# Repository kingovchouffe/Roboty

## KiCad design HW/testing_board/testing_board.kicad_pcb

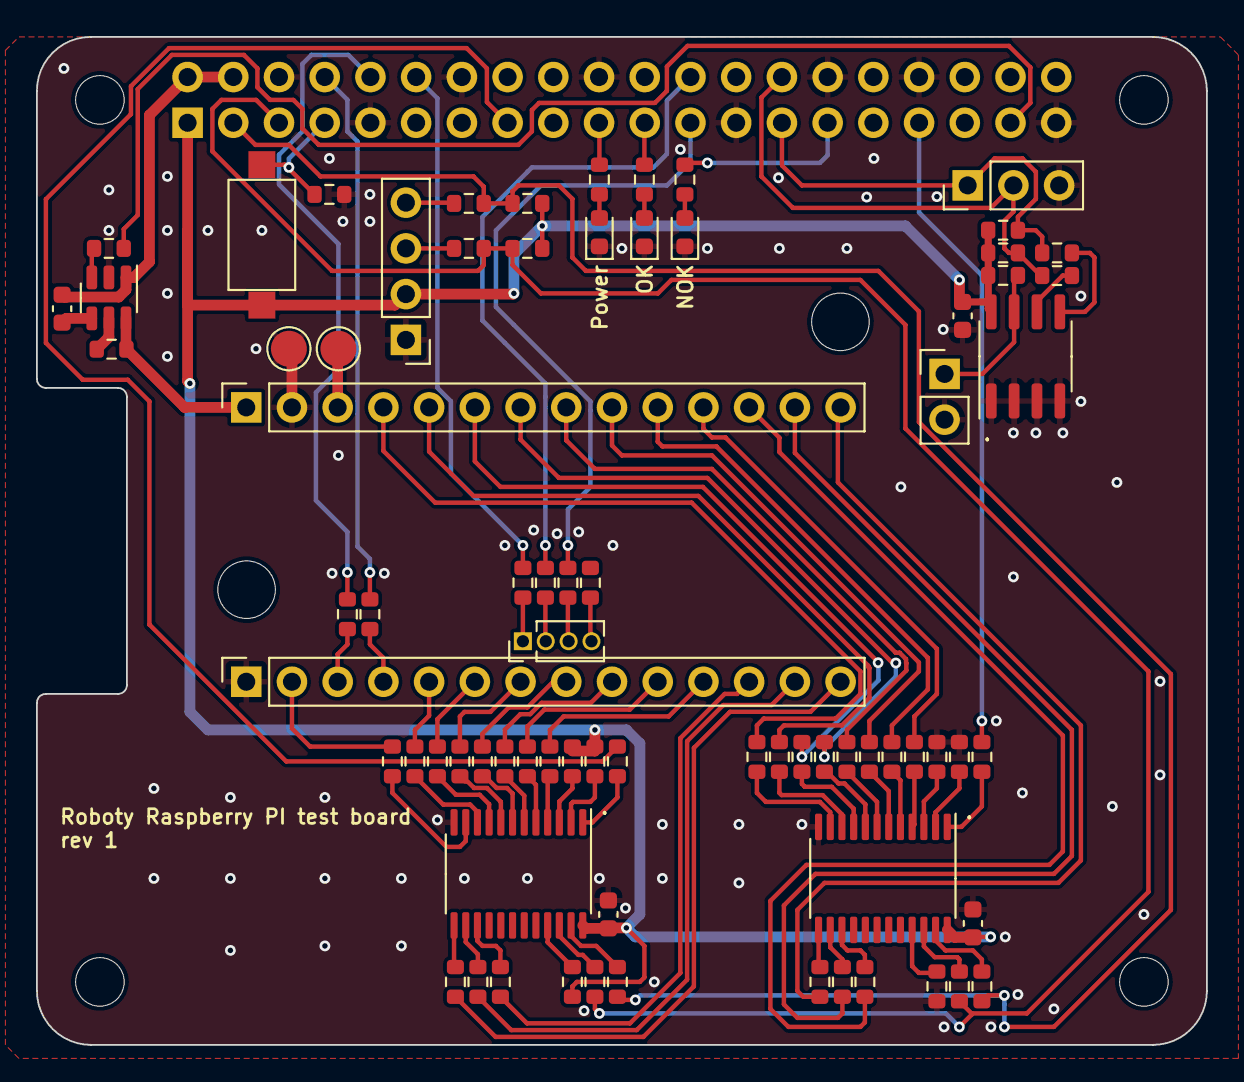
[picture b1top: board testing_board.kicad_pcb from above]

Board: 2 copper layers, 65.0 x 56.0 mm, 82 parts (1 on the bottom side), 94 nets.

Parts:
C1: C_0603_1608Metric
C2, C3, C4: 100n; C_0603_1608Metric
D1: LED_Power; LED_0603_1608Metric
D2: LED_testOK; LED_0603_1608Metric
D3: LED_testNOK; LED_0603_1608Metric
H1, H2: MountingHole; MountingHole_3.2mm_M3_ISO14580
J1: GPIO; PinSocket_2x20_P2.54mm_Vertical
J2: Left_; PinSocket_1x14_P2.54mm_Vertical
J3: Right_; PinSocket_1x14_P2.54mm_Vertical
J4: SWD; PinHeader_1x04_P1.27mm_Vertical
J5: OLED; PinHeader_1x04_P2.54mm_Vertical
J6: WP_jumper; PinHeader_1x02_P2.54mm_Vertical
J7: I2C_prob; PinHeader_1x03_P2.54mm_Vertical
MH1, MH2, MH3, MH4: MountingHole_2.7mm_M2.5
R1, R4, R5, R13, R14, R15, R16, R17, R18, R19, R20, R21, R22, R23, R24, R25, R26, R27, R28, R29, R30, R31, R32, R33, R34, R35, R42, R43, R44, R45, R46, R48: 1k; R_0603_1608Metric
R2, R3, R6, R7, R8, R9, R10, R11, R12, R36, R37, R38, R39, R40, R41, R54, R55: 0; R_0603_1608Metric
R47, R49, R50, R51, R52, R53: 10k; R_0603_1608Metric
SW1: Start; SW_SPST_CK_RS282G05A3
TP1: 3V3; TestPoint_Pad_D2.0mm
TP2: GND; TestPoint_Pad_D2.0mm
U1: TPS22917DBV; SOT-23-6
U2, U5: TCA9555PWR; TSSOP-24_4.4x7.8mm_P0.65mm
U3: CAT24C32; SOIC-8_3.9x4.9mm_P1.27mm

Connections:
+3V3: C2.1, C3.1, C4.1, J1.1, J5.2, R4.1, R5.2, R42.1, R49.2, R50.1, R51.1, R52.1, R53.1, SW1.1, U2.24 (VCC), U3.8 (VCC), U5.24 (VCC)
+5V: C1.1, J1.2, J1.4, U1.1 (VIN)
/A2: R39.1, U2.23 (SDA)
/B2: R40.2, U2.22 (SCL)
/C2: R41.1, U2.1 (~INT)
/GPIO2/SDA1: J1.3, R3.1, R36.2, R39.2, R49.1
/GPIO3/SCL1: J1.5, R2.2, R37.1, R40.1, R50.2
/GPIO4/GPCLK0: J1.7, R47.2, SW1.2
/GPIO5: J1.29, R46.1
/GPIO8/SPI0.CE0: J1.24, R10.1
/GPIO9/SPI0.MISO: J1.21, R45.1
/GPIO10/SPI0.MOSI: J1.19, R13.1
/GPIO11/SPI0.SCLK: J1.23, R11.1
/GPIO13/PWM1: J1.33, R41.2
/GPIO14/TXD0: J1.8, R6.2
/GPIO15/RXD0: J1.10, R7.1
/GPIO18/PCM.CLK: J1.12, R9.1
/GPIO22: J1.15, R38.2
/GPIO26: J1.37, R8.1
/ID_SCL: J1.28, J7.2, R53.2, R55.1
/ID_SDA: J1.27, J7.1, R52.2, R54.2
/ON/OFF: R8.2, U1.3 (ON)
/RST: J4.1, R9.2
/SWCLK: J4.3, R11.2
/SWDIO: J4.2, R10.2
/SWO: J4.4, R12.2
/UART_RX: J2.4, R6.1
/UART_TX: J2.3, R7.2
GND: C2.2, C3.2, C4.2, D1.1 (K), D2.1 (K), D3.1 (K), J1.6, J1.9, J1.14, J1.20, J1.25, J1.30, J1.34, J1.39, J2.1, J3.2, J5.1, J6.2, J7.3, R43.1, R44.2, R47.1, R48.1, TP2.1, U1.2 (GND), U2.12 (GND), U3.1 (A0), U3.2 (A1), U3.3 (A2), U3.4 (GND), U5.12 (GND)
HDR_LFT_PA0: J2.8, R17.1
HDR_LFT_PA1: J2.7, R18.2
HDR_LFT_PA2: J2.6, R19.1
HDR_LFT_PA3: J2.5, R20.2
HDR_LFT_PA4: J3.11, R25.1
HDR_LFT_PA5: J3.10, R26.2
HDR_LFT_PA6: J3.9, R22.2
HDR_LFT_PA7: J3.8, R23.1
HDR_LFT_PA8: J2.2, R21.1
HDR_LFT_PA15: J2.9, R16.2
HDR_LFT_PB4: J2.10, R15.1
HDR_RGT_PB5: J2.11, R14.2
HDR_RGT_PB7: J2.12, R29.1
HDR_RGT_PB8: J2.13, R28.2
HDR_RGT_PB9: J2.14, R27.1
HDR_RGT_PB10: J3.7, R24.2
HDR_RGT_PB12: J3.6, R30.2
HDR_RGT_PB13: J3.5, R31.1
HDR_RGT_PB14: J3.4, R32.2
HDR_RGT_PB15: J3.12, R35.1
HDR_RGT_PC0: J3.14, R33.1
HDR_RGT_PC1: J3.13, R34.2
unnamed: D1.2 (A), R13.2
unnamed: D2.2 (A), R45.2
unnamed: D3.2 (A), R46.2
unnamed: J3.3, TP1.1
unnamed: J5.3, R2.1
unnamed: J5.4, R3.2
unnamed: J6.1, R51.2, U3.7 (WP)
unnamed: C1.2, U1.4 (CT)
unnamed: R1.2, U1.5 (QOD)
unnamed: R48.2, U2.21 (A0)
unnamed: R44.1, U2.2 (A1)
unnamed: R43.2, U2.3 (A2)
unnamed: R25.2, U2.4 (P00)
unnamed: R26.1, U2.5 (P01)
unnamed: R22.1, U2.6 (P02)
unnamed: R23.2, U2.7 (P03)
unnamed: R24.1, U2.8 (P04)
unnamed: R30.1, U2.9 (P05)
unnamed: R31.2, U2.10 (P06)
unnamed: R32.1, U2.11 (P07)
unnamed: R33.2, U2.13 (P10)
unnamed: R34.1, U2.14 (P11)
unnamed: R35.2, U2.15 (P12)
unnamed: R55.2, U3.6 (SCL)
unnamed: R54.1, U3.5 (SDA)
unnamed: R4.2, U5.21 (A0)
unnamed: R5.1, U5.2 (A1)
unnamed: R42.2, U5.3 (A2)
unnamed: R14.1, U5.4 (P00)
unnamed: R15.2, U5.5 (P01)
unnamed: R16.1, U5.6 (P02)
unnamed: R17.2, U5.7 (P03)
unnamed: R18.1, U5.8 (P04)
unnamed: R19.2, U5.9 (P05)
unnamed: R20.1, U5.10 (P06)
unnamed: R21.2, U5.11 (P07)
unnamed: R27.2, U5.13 (P10)
unnamed: R28.1, U5.14 (P11)
unnamed: R29.2, U5.15 (P12)
unnamed: R37.2, U5.22 (SCL)
unnamed: R36.1, U5.23 (SDA)
unnamed: R38.1, U5.1 (~INT)
VDC: J3.1, R1.1, U1.6 (VOUT)

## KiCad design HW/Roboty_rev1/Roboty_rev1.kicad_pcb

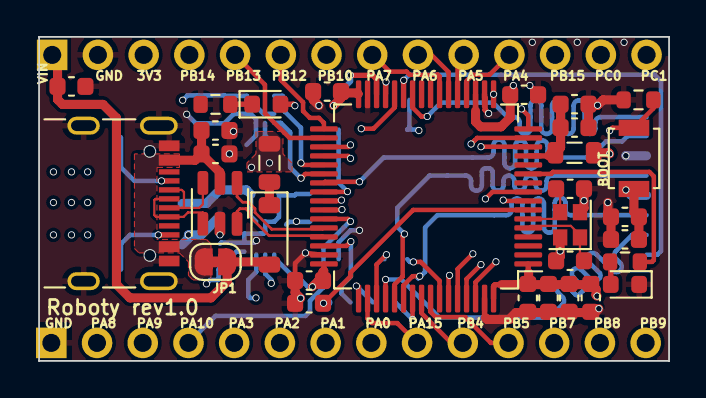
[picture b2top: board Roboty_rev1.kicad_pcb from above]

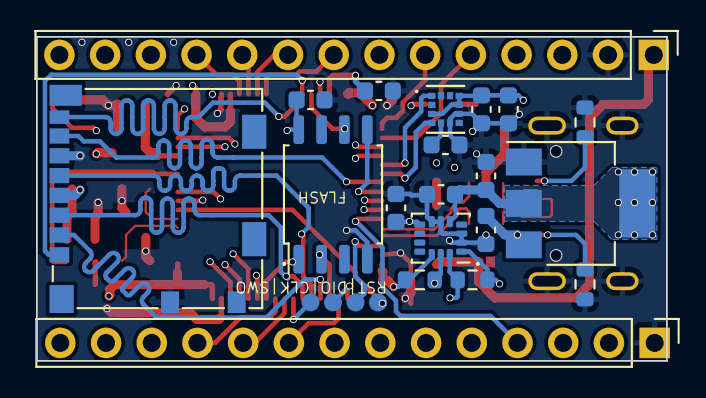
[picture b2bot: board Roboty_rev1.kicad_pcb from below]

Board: 6 copper layers, 35.0 x 18.0 mm, 55 parts (24 on the bottom side), 61 nets.

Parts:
C1, C4, C6, C11, C27: 10u; C_0603_1608Metric
C2, C3, C7, C8, C9, C10, C12, C13, C16, C19, C20, C21, C22, C23, C24, C25, C26: 100n; C_0603_1608Metric
C14: 1u; C_0603_1608Metric
C15: 4u7; C_0603_1608Metric
C17, C18: 6.8p; C_0603_1608Metric
D1: LED_33V; LED_0603_1608Metric
D2: SSS2040FL; D_SOD-123
D3: USER_LED; LED_0603_1608Metric
J1: Micro_SD_Card; microSD_HC_Molex_104031-0811
J3: USB_C_Receptacle_USB2.0; USB_C_Receptacle_GCT_USB4105-xx-A_16P_TopMnt_Horizontal
J4: Left_; PinHeader_1x14_P2.54mm_Vertical
J5: Right_; PinHeader_1x14_P2.54mm_Vertical
JP1: VUSB_VIN; SolderJumper-2_P1.3mm_Bridged_RoundedPad1.0x1.5mm
L1, L2: GZ2012D101TF; L_0805_2012Metric
R1, R2: 5.1k; R_0603_1608Metric
R3: 270; R_0603_1608Metric
R4, R6, R7: 10k; R_0603_1608Metric
R5: 1K; R_0603_1608Metric
SW2: BOOT; SW_SPST_B3U-1000P
TP1: SWO; TestPoint_Pad_D1.0mm
TP2: SWCLK; TestPoint_Pad_D1.0mm
TP3: SWDIO; TestPoint_Pad_D1.0mm
TP4: RST; TestPoint_Pad_D1.0mm
U1: STM32F446RETx; LQFP-64_10x10mm_P0.5mm
U2: NCP1117-3.3_SOT223; SOT-223-3_TabPin2
U3: USBLC6-2SC6; SOT-23-6
U4: W25Q32JVSS; SOIC-8_5.23x5.23mm_P1.27mm
U5: LSM6DS3; LGA-14_3x2.5mm_P0.5mm_LayoutBorder3x4y
U6: LIS2MDLTR; PQFN50P200X200X70-12N
Y1: 7D026000B01; Crystal_SMD_2016-4Pin_2.0x1.6mm

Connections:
+3V3: C3.1, C4.1, C7.1, C8.1, C9.1, C10.1, C11.1, C12.1, C19.1, C21.1, C22.1, C23.1, C24.1, C26.1, C27.1, D1.2 (A), J1.4 (VDD), J5.3, L2.2, R6.2, R7.1, SW2.1, U1.1 (VBAT), U1.19 (VDD), U1.32 (VDD), U1.48 (VDD), U1.64 (VDD), U2.2 (VO), U4.8 (VCC), U5.1 (SDO/SA0), U5.5 (VDDIO), U5.8 (VDD), U5.12 (CS), U6.3 (CS), U6.9 (VDD), U6.10 (VDD_IO)
+5V: C2.1, C6.1, J3.A4 (VBUS), J3.A9 (VBUS), J3.B4 (VBUS), J3.B9 (VBUS), JP1.1 (A), U3.5 (VBUS)
/I2C_SCL: R7.2, U1.37 (PC6), U5.13 (SCL), U6.1 (SCL/SPC)
/I2C_SDA: R6.1, U1.38 (PC7), U5.14 (SDA), U6.4 (SDA/SDI/SDO)
/Power&USB/USB+: U1.45 (PA12), U3.3 (I/O2)
/Power&USB/USB-: U1.44 (PA11), U3.4 (I/O2)
/mcu/BOOT0: R4.1, SW2.2, U1.60 (BOOT0)
/mcu/LED: R5.2, U1.11 (PC3)
/mcu/QSPI_BK1_CLK: U1.28 (PB2), U4.6 (CLK)
/mcu/QSPI_BK1_IO0: U1.40 (PC9), U4.5 (DI(IO0))
/mcu/QSPI_BK1_IO1: U1.51 (PC10), U4.2 (DO(IO1))
/mcu/QSPI_BK1_NCS: U1.58 (PB6), U4.1 (~CS)
/mcu/RST: C16.1, TP4.1, U1.7 (NRST)
/mcu/SDIO_CLK: J1.5 (CLK), U1.53 (PC12)
/mcu/SDIO_CMD: J1.3 (CMD), U1.54 (PD2)
/mcu/SDIO_D0: J1.7 (DAT0), U1.39 (PC8)
/mcu/SDIO_D1: J1.8 (DAT1), U1.26 (PB0)
/mcu/SDIO_D2: J1.1 (DAT2), U1.27 (PB1)
/mcu/SDIO_D3: J1.2 (DAT3/CD), U1.52 (PC11)
/mcu/SWCLK: TP2.1, U1.49 (PA14)
/mcu/SWDIO: TP3.1, U1.46 (PA13)
/mcu/SWO: TP1.1, U1.55 (PB3)
GND: C1.2, C2.2, C3.2, C4.2, C6.2, C7.2, C8.2, C9.2, C10.2, C11.2, C12.2, C13.2, C14.2, C15.2, C16.2, C17.2, C18.2, C19.2, C20.2, C21.2, C22.2, C23.2, C24.2, C25.2, C26.2, C27.2, D3.1 (K), J1.6 (VSS), J1.9 (SHIELD), J3.A1 (GND), J3.A12 (GND), J3.B1 (GND), J3.B12 (GND), J3.S1 (SHIELD), J4.1, J5.2, R1.2, R2.2, R3.1, R4.2, U1.12 (VSSA), U1.18 (VSS), U1.31 (VSS), U1.47 (VSS), U1.63 (VSS), U2.1 (GND), U3.2 (GND), U4.4 (GND), U5.2 (SDX), U5.3 (SCX), U5.6 (GND), U5.7 (GND), U6.6 (GND), U6.8 (GND), Y1.2, Y1.4
HDR_LFT_PA0: J4.8, U1.14 (PA0)
HDR_LFT_PA1: J4.7, U1.15 (PA1)
HDR_LFT_PA2: J4.6, U1.16 (PA2)
HDR_LFT_PA3: J4.5, U1.17 (PA3)
HDR_LFT_PA4: J5.11, U1.20 (PA4)
HDR_LFT_PA5: J5.10, U1.21 (PA5)
HDR_LFT_PA6: J5.9, U1.22 (PA6)
HDR_LFT_PA7: J5.8, U1.23 (PA7)
HDR_LFT_PA8: J4.2, U1.41 (PA8)
HDR_LFT_PA9: J4.3, U1.42 (PA9)
HDR_LFT_PA10: J4.4, U1.43 (PA10)
HDR_LFT_PA15: J4.9, U1.50 (PA15)
HDR_LFT_PB4: J4.10, U1.56 (PB4)
HDR_RGT_PB5: J4.11, U1.57 (PB5)
HDR_RGT_PB7: J4.12, U1.59 (PB7)
HDR_RGT_PB8: J4.13, U1.61 (PB8)
HDR_RGT_PB9: J4.14, U1.62 (PB9)
HDR_RGT_PB10: J5.7, U1.29 (PB10)
HDR_RGT_PB12: J5.6, U1.33 (PB12)
HDR_RGT_PB13: J5.5, U1.34 (PB13)
HDR_RGT_PB14: J5.4, U1.35 (PB14)
HDR_RGT_PB15: J5.12, U1.36 (PB15)
HDR_RGT_PC0: J5.14, U1.8 (PC0)
HDR_RGT_PC1: J5.13, U1.9 (PC1)
unnamed: D1.1 (K), R3.2
unnamed: D2.1 (K), L1.1
unnamed: D3.2 (A), R5.1
unnamed: J3.A5 (CC1), R1.1
unnamed: J3.B5 (CC2), R2.1
unnamed: J3.A6 (D+), J3.B6 (D+), U3.1 (I/O1)
unnamed: J3.A7 (D-), J3.B7 (D-), U3.6 (I/O1)
unnamed: C17.1, U1.5 (PH0), Y1.1
unnamed: C18.1, U1.6 (PH1), Y1.3
unnamed: C15.1, U1.30 (VCAP_1)
unnamed: C1.1, L1.2, U2.3 (VI)
unnamed: C25.1, U6.5 (C1)
VDC: C20.1, D2.2 (A), J5.1, JP1.2 (B)
VDDA: C13.1, C14.1, L2.1, U1.13 (VDDA)

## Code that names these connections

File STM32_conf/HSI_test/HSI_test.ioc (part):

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Mcu.Name=STM32F446R(C-E)Tx
Mcu.Package=LQFP64
Mcu.UserName=STM32F446RETx
PA13.Mode=Trace_Asynchronous_SW
PA13.Signal=SYS_JTMS-SWDIO
PA14.Mode=Trace_Asynchronous_SW
PA14.Signal=SYS_JTCK-SWCLK
PB0.Mode=SD_4_bits_Wide_bus
PB0.Signal=SDIO_D1
PB1.Mode=SD_4_bits_Wide_bus
PB1.Signal=SDIO_D2
PB2.Mode=Single Bank 1 2IOs
PB2.Signal=QUADSPI_CLK
PB3.Mode=Trace_Asynchronous_SW
PB3.Signal=SYS_JTDO-SWO
PB6.Mode=Single Bank 1 2IOs
PB6.Signal=QUADSPI_BK1_NCS
PC10.Mode=Single Bank 1 2IOs
PC10.Signal=QUADSPI_BK1_IO1
PC11.Mode=SD_4_bits_Wide_bus
PC11.Signal=SDIO_D3
PC12.Mode=SD_4_bits_Wide_bus
PC12.Signal=SDIO_CK
PC6.Mode=I2C
PC6.Signal=FMPI2C1_SCL
PC7.Mode=I2C
PC7.Signal=FMPI2C1_SDA
PC8.Mode=SD_4_bits_Wide_bus
PC8.Signal=SDIO_D0
PC9.Mode=Single Bank 1 2IOs
PC9.Signal=QUADSPI_BK1_IO0
PD2.Mode=SD_4_bits_Wide_bus
PD2.Signal=SDIO_CMD
RCC.HSE_VALUE=16000000
RCC.SYSCLKFreq_VALUE=180000000
RCC.SYSCLKSource=RCC_SYSCLKSOURCE_PLLCLK
board=custom

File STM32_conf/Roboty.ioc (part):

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Mcu.Name=STM32F446R(C-E)Tx
Mcu.Package=LQFP64
Mcu.UserName=STM32F446RETx
PA11.Mode=Device_Only
PA11.Signal=USB_OTG_FS_DM
PA12.Mode=Device_Only
PA12.Signal=USB_OTG_FS_DP
PA13.Mode=Trace_Asynchronous_SW
PA13.Signal=SYS_JTMS-SWDIO
PA14.Mode=Trace_Asynchronous_SW
PA14.Signal=SYS_JTCK-SWCLK
PB0.Mode=SD_4_bits_Wide_bus
PB0.Signal=SDIO_D1
PB3.Mode=Trace_Asynchronous_SW
PB3.Signal=SYS_JTDO-SWO
PC10.Mode=SD_4_bits_Wide_bus
PC10.Signal=SDIO_D2
PC11.Mode=SD_4_bits_Wide_bus
PC11.Signal=SDIO_D3
PC12.Mode=SD_4_bits_Wide_bus
PC12.Signal=SDIO_CK
PC6.Mode=I2C
PC6.Signal=FMPI2C1_SCL
PC7.Mode=I2C
PC7.Signal=FMPI2C1_SDA
PC8.Mode=SD_4_bits_Wide_bus
PC8.Signal=SDIO_D0
PD2.Mode=SD_4_bits_Wide_bus
PD2.Signal=SDIO_CMD
PH0-OSC_IN.Mode=HSE-External-Oscillator
PH0-OSC_IN.Signal=RCC_OSC_IN
PH1-OSC_OUT.Mode=HSE-External-Oscillator
PH1-OSC_OUT.Signal=RCC_OSC_OUT
RCC.HSE_VALUE=26000000
RCC.SYSCLKFreq_VALUE=180000000
RCC.SYSCLKSource=RCC_SYSCLKSOURCE_PLLCLK
board=custom

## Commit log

2024-08-05 add sd card file library+ new HW version
